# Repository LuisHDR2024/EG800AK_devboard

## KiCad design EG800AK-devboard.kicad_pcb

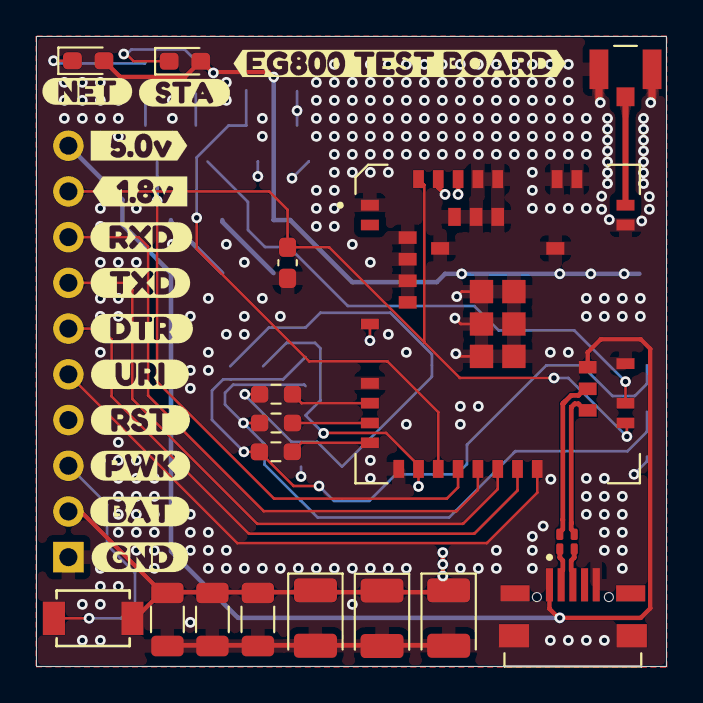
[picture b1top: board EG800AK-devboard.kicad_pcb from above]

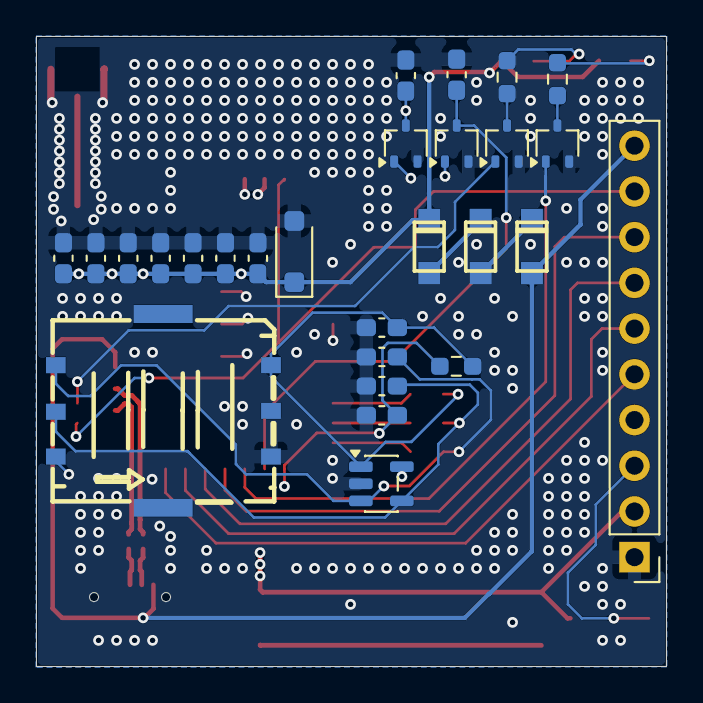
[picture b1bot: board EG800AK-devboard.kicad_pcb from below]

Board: 4 copper layers, 35.0 x 35.0 mm, 58 parts (27 on the bottom side), 32 nets.

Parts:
C1, C2, C3: 33pF; C_0603_1608Metric_Pad1.08x0.95mm_HandSolder
C4, C11: 100nf; C_0603_1608Metric_Pad1.08x0.95mm_HandSolder
C5, C6, C12: 10nf; C_0603_1608Metric_Pad1.08x0.95mm_HandSolder
C7, C8, C17: 100uF; CP_EIA-3528-21_Kemet-B
C9, C16: 47uf; C_0603_1608Metric_Pad1.08x0.95mm_HandSolder
C10: 33pf; C_0603_1608Metric_Pad1.08x0.95mm_HandSolder
C13: 0.1uf; C_0603_1608Metric_Pad1.08x0.95mm_HandSolder
C14: 1uf; C_0603_1608Metric_Pad1.08x0.95mm_HandSolder
C15: 10uf; C_0603_1608Metric_Pad1.08x0.95mm_HandSolder
C18, C19, C20: 100uf; C_1206_3216Metric
D1: ESDA6V1SC5; SOT-23-5
D2, D3, D4: KUU SS36; KUU_SS36_foot
D5: SMFJ5.0A; D_SOD-123F
D6, D7: LED; LED_0603_1608Metric_Pad1.05x0.95mm_HandSolder
J1: U.FL-R-SMT_10_; U.FL-R-SMT_10_-foot
J2: MICROQTJ; MICROQTJ-foot
J4: Conn_01x11_Pin; PinHeader_1x10_P2.54mm_Vertical
NANO-SIM-0501A-P1: NANO-SIM-0501A-P; nano-sim-0501a-p_foot
Q1, Q2, Q4, Q5: DTC143ZUAT106; SOT-323_SC-70
R1, R2, R3: 0; R_0603_1608Metric_Pad0.98x0.95mm_HandSolder
R4: 15k; R_0603_1608Metric_Pad0.98x0.95mm_HandSolder
R5, R6: 22; R_0201_0603Metric_Pad0.64x0.40mm_HandSolder
R7, R8: 2.2k; R_0603_1608Metric_Pad0.98x0.95mm_HandSolder
SW1: TS-1088-AR02016; SW-SMD_L3.9-W3.0-P4.45
U1: EG800KEULC-I03-SNNSA; Quectel_EG800K_foot
kibuzzard-6A62D44D: G***; kibuzzard-6A62D44D
kibuzzard-6A62D453: G***; kibuzzard-6A62D453
kibuzzard-6A799EF0: G***; kibuzzard-6A799EF0
kibuzzard-6A799EF5: G***; kibuzzard-6A799EF5
kibuzzard-6A799F00: G***; kibuzzard-6A799F00
kibuzzard-6A799F0B: G***; kibuzzard-6A799F0B
kibuzzard-6A799F05: G***; kibuzzard-6A799F05
kibuzzard-6A799F5E: G***; kibuzzard-6A799F5E
kibuzzard-6A799F12: G***; kibuzzard-6A799F12
kibuzzard-6A799F21: G***; kibuzzard-6A799F21
kibuzzard-6A799F96: G***; kibuzzard-6A799F96
kibuzzard-6A799FB4: G***; kibuzzard-6A799FB4
kibuzzard-6AB97A40: G***; kibuzzard-6AB97A40

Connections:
+5V: D2.A, J2.1 (VCC), J4.10, U1.61 (USB_VBUS)
/DC 3.8v supply: C7.1, C8.1, C9.2, C10.2, C11.2, C12.2, C13.2, C14.2, C15.2, C17.1, C18.2, C19.2, C20.2, D4.C, D5.1 (K), D6.2 (A), D7.2 (A), J4.2, SW1.1, U1.42 (VBAT), U1.43 (VBAT__1)
/EG800K.MAIN_DTR: J4.6, U1.19 (MAIN_DTR)
/EG800K.NET_STATUS: Q5.1 (B), U1.16 (NET_STATUS)
/EG800K.PWRKEY: C5.2, Q1.3 (C), U1.7 (PWRKEY)
/EG800K.RESET: C6.2, Q2.3 (C), U1.15 (~RESET)
/EG800K.STATUS: Q4.1 (B), U1.25 (STATUS)
/EG800K.UART1_RXD: J4.8, U1.17 (MAIN_RXD)
/EG800K.UART1_Ri: J4.5, U1.20 (MAIN_RI)
/EG800K.UART1_TXD: J4.7, U1.18 (MAIN_TXD)
/EG800K.USB_D+: R6.2, U1.59 (USB_DP)
/EG800K.USB_D-: R5.2, U1.60 (USB_DM)
/EG800K.VDD_ETX: C16.2, J4.9, U1.24 (VDD_EXT), U1.44 (RESERVED_1__10)
/HOST.EG800K.PWRKEY: J4.3, Q1.1 (B), SW1.2
/HOST.EG800K.RESET: J4.4, Q2.1 (B)
/RF_ANT: J1.SIG, U1.35 (ANT_MAIN)
/SIM_CLK: R2.1, U1.13 (USIM_CLK)
/SIM_DATA: R3.1, U1.11 (USIM_DATA)
/SIM_RST: R1.1, U1.12 (USIM_RST)
/SIM_VDD: C4.2, D1.5 (K), NANO-SIM-0501A-P1.C1 (VCC), R4.2, U1.14 (USIM_VDD)
/USB+: J2.3 (D+), R6.1
/USB-: J2.2 (D-), R5.1
GND: C1.1, C2.1, C3.1, C4.1, C5.1, C6.1, C7.2, C8.2, C9.1, C10.1, C11.1, C12.1, C13.1, C14.1, C15.1, C16.1, C17.2, C18.1, C19.1, C20.1, D1.2 (A), D5.2 (A), J1.G1, J1.G2, J2.5 (GND), J4.1, NANO-SIM-0501A-P1.C5 (GND), Q1.2 (E), Q2.2 (E), Q4.2 (E), Q5.2 (E), U1.1 (GND_1), U1.10 (GND_1__1), U1.27 (GND_1__2), U1.34 (GND_1__3), U1.36 (GND_1__4), U1.37 (GND_1__5), U1.40 (GND_1__6), U1.41 (GND_1__7), U1.45 (GND_1__8), U1.46 (GND_1__9), U1.47 (GND_1__10), U1.48 (GND_1__11), U1.70 (GND_2), U1.71 (GND_2__1), U1.72 (GND_2__2), U1.73 (GND_2__3), U1.88 (GND_2__4), U1.89 (GND_2__5), U1.90 (GND_2__6), U1.91 (GND_2__7), U1.92 (GND_2__8), U1.93 (GND_2__9), U1.94 (GND_2__10), U1.95 (GND_2__11)
unnamed: D2.C, D3.A
unnamed: D3.C, D4.A
unnamed: D6.1 (K), R7.2
unnamed: D7.1 (K), R8.2
unnamed: C2.2, D1.3 (K), NANO-SIM-0501A-P1.C3 (CLK), R2.2
unnamed: C1.2, D1.1 (K), NANO-SIM-0501A-P1.C7 (I/O), R3.2, R4.1
unnamed: C3.2, D1.4 (K), NANO-SIM-0501A-P1.C2 (RST), R1.2
unnamed: Q4.3 (C), R7.1
unnamed: Q5.3 (C), R8.1
